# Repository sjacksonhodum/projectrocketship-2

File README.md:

# projectrocketship
## But this time version 2 :0

Check R1 on sensor board. 732kohm??? add whatever the right value is to the current lcsc cart

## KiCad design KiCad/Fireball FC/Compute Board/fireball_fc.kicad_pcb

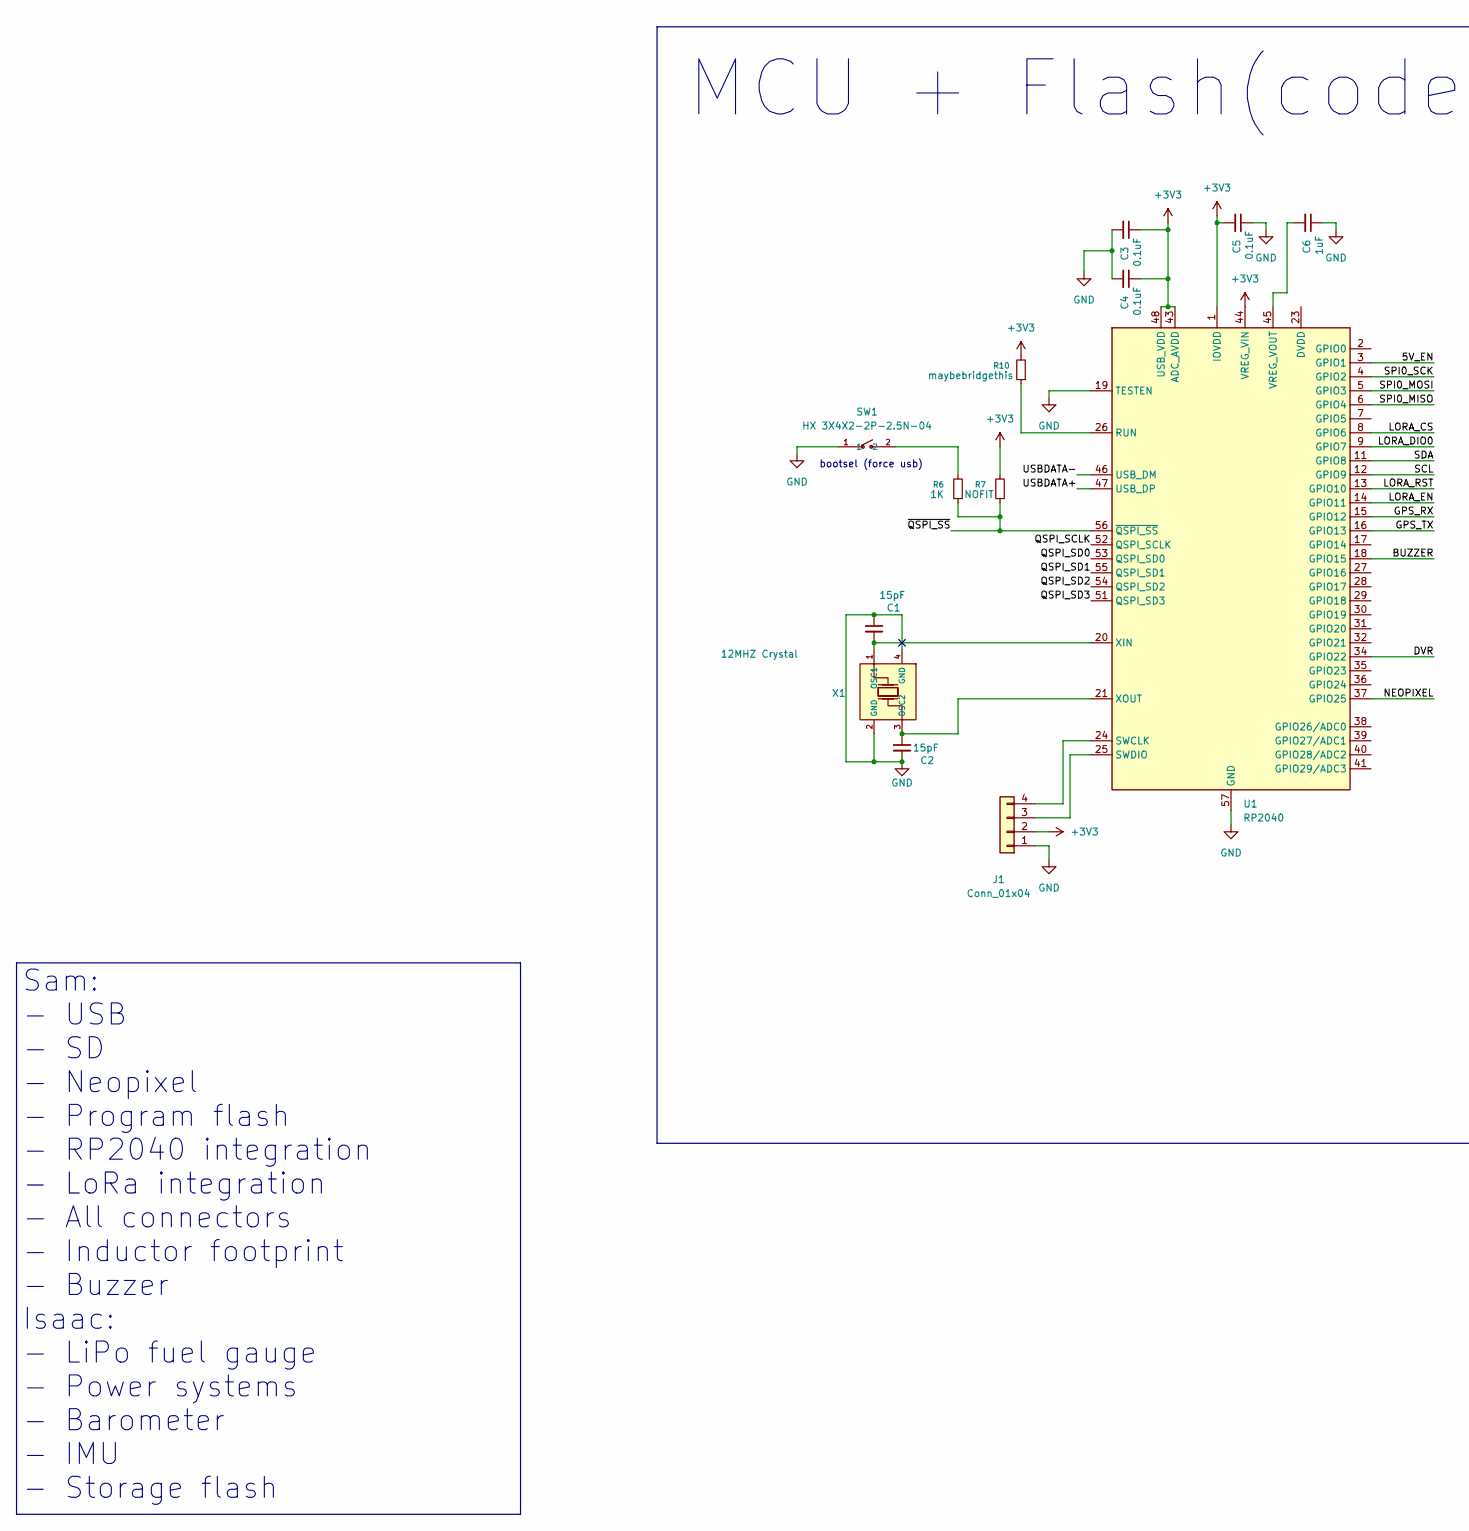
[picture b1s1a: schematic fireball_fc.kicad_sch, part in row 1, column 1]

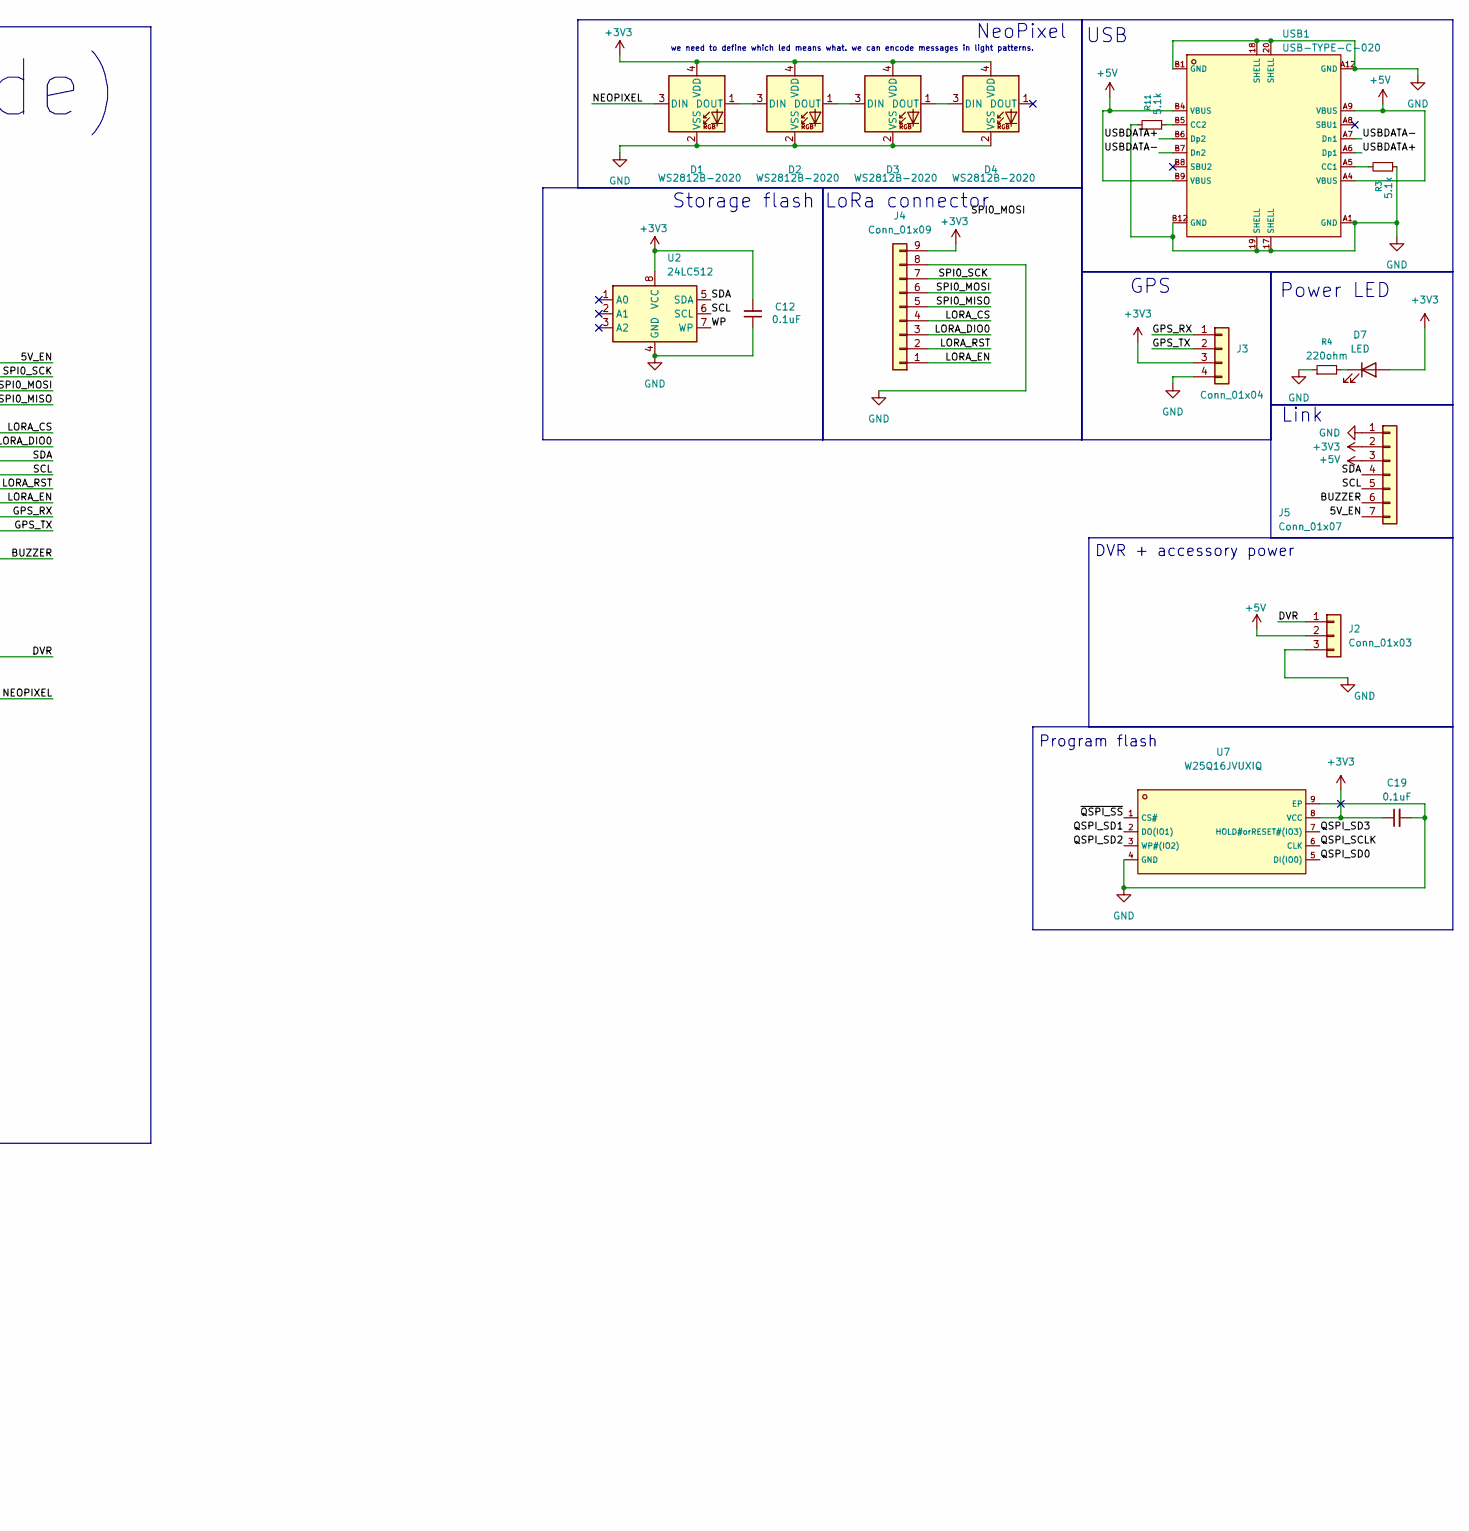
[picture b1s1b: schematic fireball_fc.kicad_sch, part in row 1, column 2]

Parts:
C1, C2: 15pF; C_0402_1005Metric
C3, C4, C5, C12, C19: 0.1uF; C_0402_1005Metric
C6: 1uF; C_0603_1608Metric
D1, D2, D3, D4: WS2812B-2020; LED_WS2812B-2020_PLCC4_2.0x2.0mm
D7: LED; LED_0805_2012Metric
J1, J3: Conn_01x04; PinHeader_1x04_P2.00mm_Vertical
J2: Conn_01x03; PinHeader_1x03_P2.00mm_Vertical
J4: Conn_01x09; PinHeader_1x09_P2.00mm_Vertical
J5: Conn_01x07; PinSocket_1x07_P2.00mm_Vertical
R3, R11: 5.1k; R_0402_1005Metric
R4: 220ohm; R_0402_1005Metric
R6: 1K; R_0402_1005Metric
R7: NOFIT; R_0402_1005Metric
R10: maybebridgethis; R_0402_1005Metric
SW1: HX 3X4X2-2P-2.5N-04; C54407262_SW-SMD_L4_0-W3_0-LS5_0; LCSC C54407262
U1: RP2040; QFN-56-1EP_7x7mm_P0.4mm_EP3.2x3.2mm
U2: 24LC512; SOIC-8-1EP_3.9x4.9mm_P1.27mm_EP2.29x3mm
U7: W25Q16JVUXIQ; C2843335_USON-8_L3_0-W2_0-P0_50-BL-EP; LCSC C2843335
USB1: USB-TYPE-C-020; C2927040_USB-SMD_USB-TYPE-C-020; LCSC C2927040
X1: 12MHZ Crystal; C157341_OSC-SMD_4P-L5_0-W3_2-BL; LCSC C5575013

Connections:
+3V3: C3.1, C4.1, C5.2, C12.2, C19.1, D1.4 (VDD), D2.4 (VDD), D3.4 (VDD), D4.4 (VDD), D7.2 (A), J1.2, J3.3, J4.9, J5.2, R7.2, R10.2, U1.1 (IOVDD), U1.10 (IOVDD), U1.22 (IOVDD), U1.33 (IOVDD), U1.42 (IOVDD), U1.43 (ADC_AVDD), U1.44 (VREG_VIN), U1.48 (USB_VDD), U1.49 (IOVDD), U2.8 (VCC), U7.8 (VCC); also elsewhere on the board
+5V: J2.2, J5.3, USB1.A4 (VBUS), USB1.A9 (VBUS), USB1.B4 (VBUS), USB1.B9 (VBUS)
/5V_EN: J5.7, U1.3 (GPIO1)
/BUZZER: J5.6, U1.18 (GPIO15)
/DVR: J2.1, U1.34 (GPIO22)
/GPS_RX: J3.1, U1.15 (GPIO12)
/GPS_TX: J3.2, U1.16 (GPIO13)
/LORA_CS: J4.4, U1.8 (GPIO6)
/LORA_DIO0: J4.3, U1.9 (GPIO7)
/LORA_EN: J4.1, U1.14 (GPIO11)
/LORA_RST: J4.2, U1.13 (GPIO10)
/NEOPIXEL: D1.3 (DIN), U1.37 (GPIO25)
/QSPI_SCLK: U1.52 (QSPI_SCLK), U7.6 (CLK)
/QSPI_SD0: U1.53 (QSPI_SD0), U7.5 (DI(IO0))
/QSPI_SD1: U1.55 (QSPI_SD1), U7.2 (DO(IO1))
/QSPI_SD2: U1.54 (QSPI_SD2), U7.3 (WP#(IO2))
/QSPI_SD3: U1.51 (QSPI_SD3), U7.7 (HOLD#orRESET#(IO3))
/SCL: J5.5, U1.12 (GPIO9), U2.6 (SCL)
/SDA: J5.4, U1.11 (GPIO8), U2.5 (SDA)
/SPI0_MISO: J4.5, U1.6 (GPIO4)
/SPI0_MOSI: J4.6, U1.5 (GPIO3)
/SPI0_SCK: J4.7, U1.4 (GPIO2)
/USBDATA+: U1.47 (USB_DP), USB1.A6 (Dp1), USB1.B6 (Dp2)
/USBDATA-: U1.46 (USB_DM), USB1.A7 (Dn1), USB1.B7 (Dn2)
/WP: U2.7 (WP)
/~QSPI_SS: R6.1, R7.1, U1.56 (~QSPI_SS), U7.1 (CS#)
GND: C1.1, C2.2, C3.2, C4.2, C5.1, C6.1, C12.1, C19.2, D1.2 (VSS), D2.2 (VSS), D3.2 (VSS), D4.2 (VSS), J1.1, J2.3, J3.4, J4.8, J5.1, R3.1, R4.1, R11.2, SW1.1, U1.19 (TESTEN), U1.57 (GND), U2.4 (GND), U7.4 (GND), U7.9 (EP), USB1.17 (SHELL), USB1.18 (SHELL), USB1.19 (SHELL), USB1.20 (SHELL), USB1.A1 (GND), USB1.A12 (GND), USB1.B1 (GND), USB1.B12 (GND), X1.2 (GND), X1.4 (GND); also elsewhere on the board
unnamed: D1.1 (DOUT), D2.3 (DIN)
unnamed: D2.1 (DOUT), D3.3 (DIN)
unnamed: D3.1 (DOUT), D4.3 (DIN)
unnamed: D7.1 (K), R4.2
unnamed: J1.3, U1.25 (SWDIO)
unnamed: J1.4, U1.24 (SWCLK)
unnamed: R6.2, SW1.2
unnamed: U1.23 (DVDD), U1.50 (DVDD)
unnamed: R10.1, U1.26 (RUN)
unnamed: C6.2, U1.45 (VREG_VOUT)
unnamed: C1.2, U1.20 (XIN), X1.1 (OSC1)
unnamed: C2.1, U1.21 (XOUT), X1.3 (OSC2)
unnamed: R3.2, USB1.A5 (CC1)
unnamed: R11.1, USB1.B5 (CC2)

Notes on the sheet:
Storage flash
MCU + Flash(code)
DVR + accessory power
bootsel (force usb)
USB
LoRa connector
we need to define which led means what. we can encode messages in light patterns.
Power LED
NeoPixel
Link
Program flash
GPS
Sam: - USB - SD - Neopixel - Program flash - RP2040 integration - LoRa integration - All connectors - Inductor footprint - Buzzer Isaac: - LiPo fuel gauge - Power systems - Barometer - IMU - Storage flash

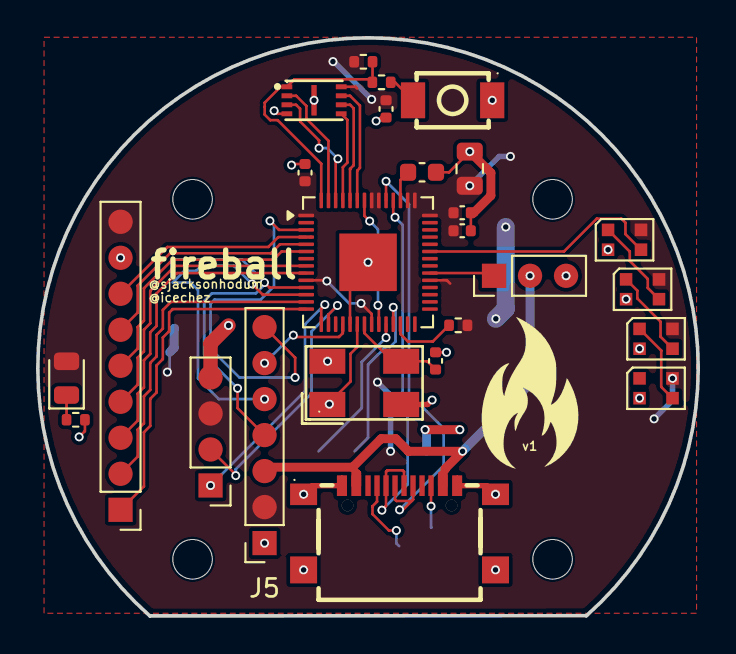
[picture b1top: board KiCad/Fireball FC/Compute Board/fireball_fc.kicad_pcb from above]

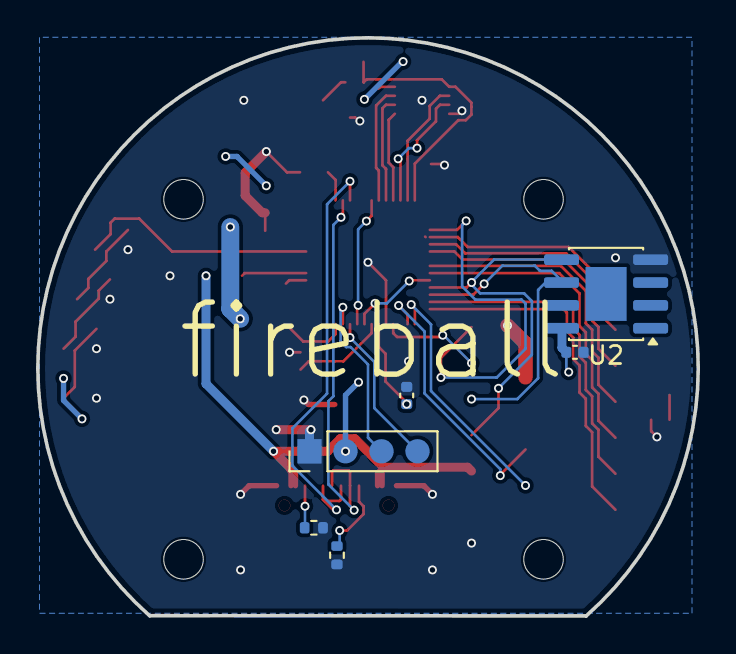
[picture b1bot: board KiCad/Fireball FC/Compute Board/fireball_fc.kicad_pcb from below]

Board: 2 copper layers, 36.7 x 32.1 mm, 35 parts (6 on the bottom side), 40 nets.

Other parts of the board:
C22: 10uF; C_0805_2012Metric
M1, M2, M3, M4: MountingHole_2.2mm_M2

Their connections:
+3V3: C22.2; also elsewhere on the board
GND: C22.1; also elsewhere on the board

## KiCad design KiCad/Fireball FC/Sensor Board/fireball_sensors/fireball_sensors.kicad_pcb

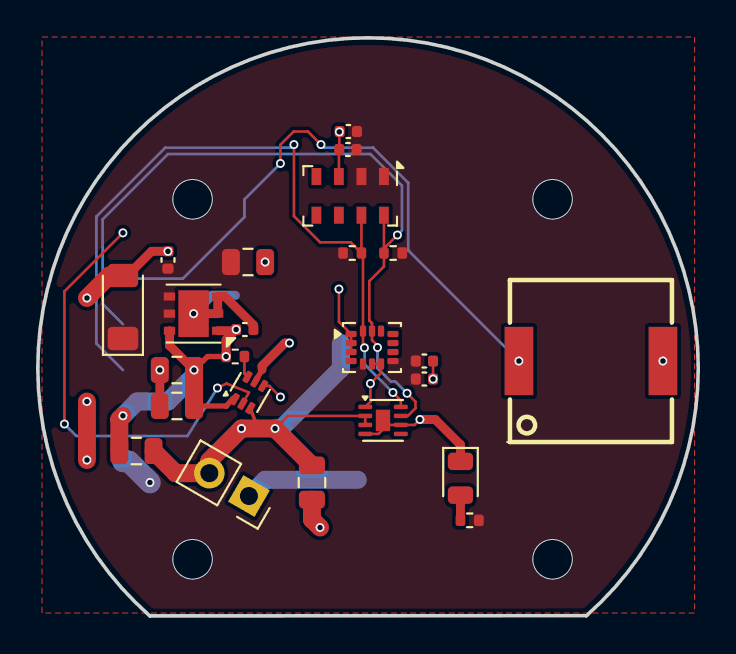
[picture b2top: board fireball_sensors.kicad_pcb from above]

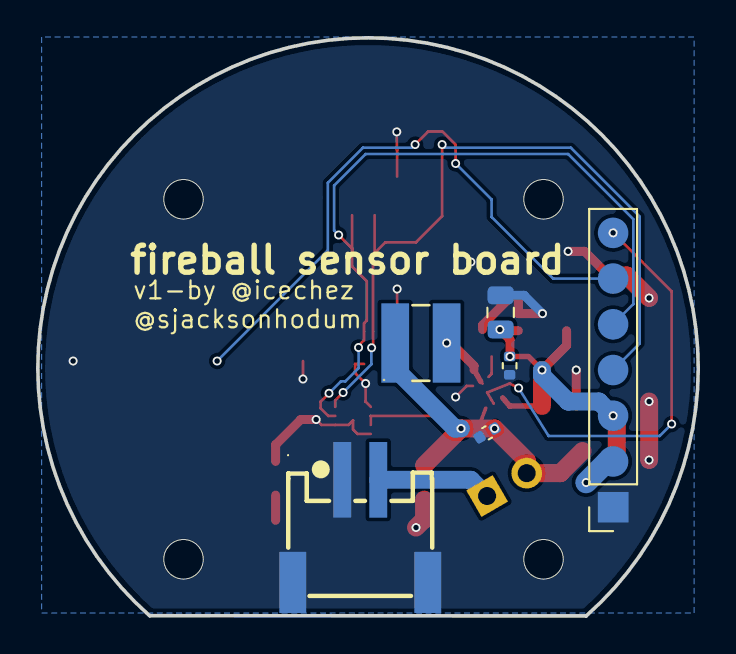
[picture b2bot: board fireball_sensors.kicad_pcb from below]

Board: 2 copper layers, 36.7 x 32.1 mm, 34 parts (6 on the bottom side), 12 nets.

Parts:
BUZ1: CPT-9019S-SMT-TR; C95163_BUZ-SMD_L9_0-W9_0-P8_00-LS9_3
C7, C13, C15, C16, C17, C18, C20: 0.1uF; C_0402_1005Metric
C8: 10uF; C_0805_2012Metric
C9, C10: 22uF; C_0805_2012Metric
C11: 4.7uF; C_0805_2012Metric
C14: 1uF; C_0805_2012Metric
CN1: HDGC2001WR-S-2P; C2936224_CONN-SMD_2P-P2_00_HDGC_HDGC2001WR-S-2P
D1: LED_Small; LED_0805_2012Metric
D5: BZV55B5V1; D_MiniMELF
D6: D; C_0805_2012Metric
J1: Conn_01x07; PinSocket_1x07_P2.54mm_Vertical
L2: FTC404030S1R0MGCA; C39676079_IND-SMD_L4_1-W4_1_SPM40XX
M1, M2, M3, M4: MountingHole_2.2mm_M2
R1: 732k; R_0402_1005Metric
R2: 100k; R_0402_1005Metric
R3: R_Small; R_0402_1005Metric
R8, R9: 4.7k; R_0402_1005Metric
SW2: MAIN POWER; PinSocket_1x02_P2.54mm_Vertical
U2: MAX17048G; TDFN-8-1EP_2x2mm_P0.5mm_EP0.8x1.2mm
U3: TPS61023; SOT-563
U5: NCP708; DFN-6-1EP_3x3mm_P0.95mm_EP1.7x2.6mm
U8: LSM6DSO; LGA-14_3x2.5mm_P0.5mm_LayoutBorder3x4y
U9: MS5607-02BA; LGA-8_3x5mm_P1.25mm

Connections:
+3V3: C11.1, C13.2, C16.2, C17.2, C18.1, C20.1, D5.1 (K), J1.2, R3.1, R8.2, R9.2, U5.4 (OUT), U5.5 (OUT_S), U8.5 (VDDIO), U8.8 (VDD), U9.1 (VDD), U9.2 (PS)
+5V: C9.2, C10.2, C14.1, C15.2, D6.1 (K), J1.3, R1.2, R2.2, U3.1 (FB), U5.1 (EN), U5.6 (IN)
+BATT: C7.2, C8.2, D6.2 (A), L2.1, SW2.2 (B), U2.2 (CELL), U2.3 (VDD), U3.3 (VIN)
/5V_EN: J1.7, U3.2 (EN)
/BUZZER: BUZ1.1 (+), J1.6
/SCL: J1.5, R9.1, U2.7 (SCL), U8.13 (SCL), U9.8 (SCLK)
/SDA: J1.4, R8.1, U2.8 (SDA), U8.14 (SDA), U9.7 (SDI/SDA)
GND: BUZ1.2 (-), C7.1, C8.1, C9.1, C10.1, C11.2, C13.1, C14.2, C15.1, C16.1, C17.1, C18.2, C20.2, CN1.1, CN1.3, CN1.4, D1.1 (K), D5.2 (A), J1.1, R2.1, U2.1 (CTG), U2.4 (GND), U2.6 (Q), U2.9 (PAD), U3.4 (GND), U5.2 (GND), U5.3 (N/C), U5.7 (PAD), U8.1 (SDO/SA0), U8.2 (SDX), U8.3 (SCX), U8.6 (GND), U8.7 (GND), U9.3 (GND)
unnamed: D1.2 (A), R3.2
unnamed: CN1.2, SW2.1 (A)
unnamed: L2.2, U3.5 (SW)
unnamed: R1.1, U3.6 (VOUT)

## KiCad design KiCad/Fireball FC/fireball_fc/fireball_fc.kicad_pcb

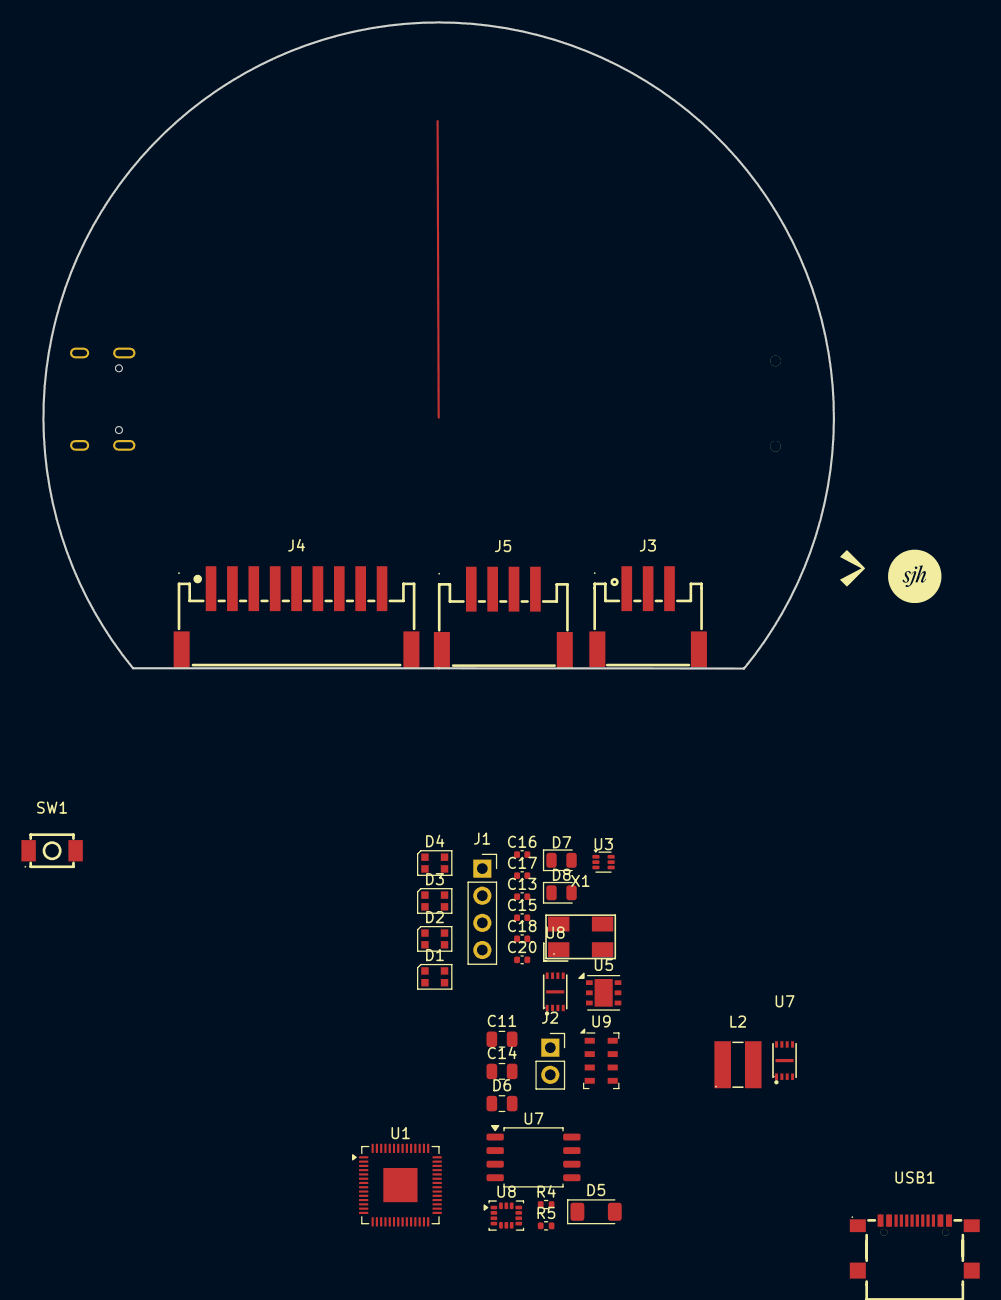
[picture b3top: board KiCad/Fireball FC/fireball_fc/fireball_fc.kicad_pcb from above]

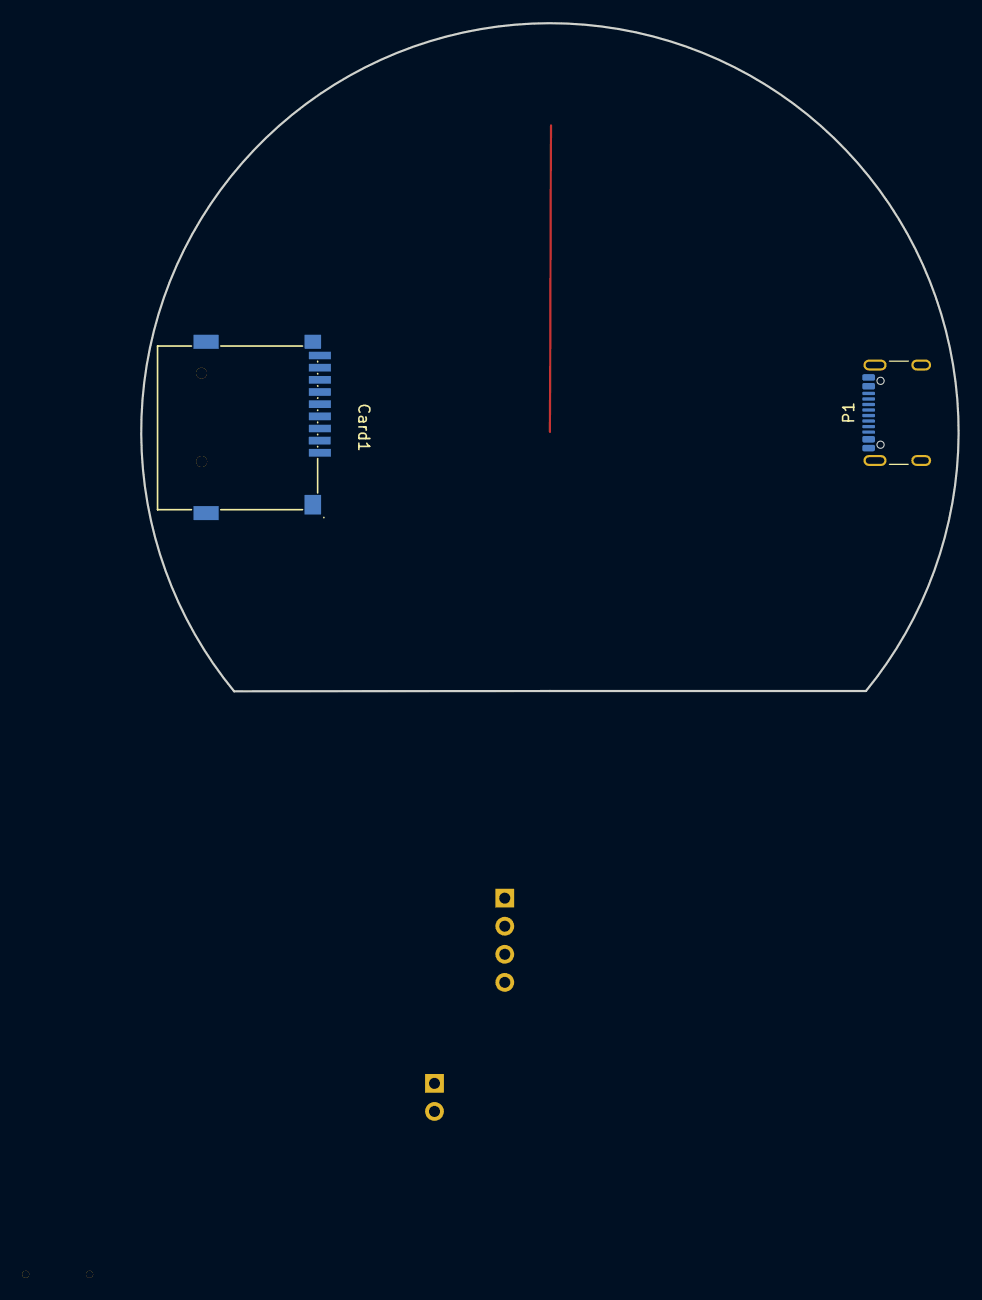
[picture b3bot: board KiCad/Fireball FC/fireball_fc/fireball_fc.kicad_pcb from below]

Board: 2 copper layers, 74.0 x 60.5 mm, 37 parts (2 on the bottom side), 29 nets, no tracks yet.

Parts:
C11: 4.7uF; C_0805_2012Metric
C13, C15, C16, C17, C18, C20: 0.1uF; C_0402_1005Metric
C14: 1uF; C_0805_2012Metric
Card1: HYC77-TF09-200; C341092_TF-SMD_HYC77-TF09-200
D1, D2, D3, D4: WS2812B-2020; LED_WS2812B-2020_PLCC4_2.0x2.0mm
D5: BZV55B5V1; D_MiniMELF
D6: D; C_0805_2012Metric
D7, D8: LED; LED_0805_2012Metric
J1: Conn_01x04; PinSocket_1x04_P2.54mm_Vertical
J2: Conn_01x02; PinSocket_1x02_P2.54mm_Vertical
J3: HDGC2001WR-S-3P; C2936225_CONN-SMD_3P-P2_00_HDGC_HDGC2001WR-S-3P
J4: HDGC2001WR-S-9P; C5175304_CONN-SMD_9P-P2_00_HDGC_HDGC2001WR-S-9P
J5: HDGC2001WR-S-4P; C2936226_CONN-SMD_4P-P2_00_HDGC_HDGC2001WR-S-4P
L2: FTC404030S1R0MGCA; C39676079_IND-SMD_L4_1-W4_1_SPM40XX
P1: USB_C_Plug_USB2.0; USB_C_Receptacle_GCT_USB4105-xx-A_16P_TopMnt_Horizontal
R4, R5: 220ohm; R_0402_1005Metric
SW1: HX 3X4X2-2P-2.5N-04; C54407262_SW-SMD_L4_0-W3_0-LS5_0
U1: RP2040; QFN-56-1EP_7x7mm_P0.4mm_EP3.2x3.2mm
U3: TPS61023; SOT-563
U5: NCP708; DFN-6-1EP_3x3mm_P0.95mm_EP1.7x2.6mm
U7: W25Q128JVS; SOIC-8_5.3x5.3mm_P1.27mm
U7#2, U8#2: W25Q16JVUXIQ; C2843335_USON-8_L3_0-W2_0-P0_50-BL-EP
U8: LSM6DSO; LGA-14_3x2.5mm_P0.5mm_LayoutBorder3x4y
U9: MS5607-02BA; LGA-8_3x5mm_P1.25mm
USB1: USB-TYPE-C-020; C2927040_USB-SMD_USB-TYPE-C-020
X1: 12MHZ Crystal; C157341_OSC-SMD_4P-L5_0-W3_2-BL

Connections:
+3V3: C11.1, C13.2, C16.2, C17.2, C18.1, C20.1, D1.4 (VDD), D2.4 (VDD), D3.4 (VDD), D4.4 (VDD), D5.1 (K), D7.2 (A), J1.2, J4.9, U1.1 (IOVDD), U1.10 (IOVDD), U1.22 (IOVDD), U1.33 (IOVDD), U1.42 (IOVDD), U1.43 (ADC_AVDD), U1.44 (VREG_VIN), U1.48 (USB_VDD), U1.49 (IOVDD), U5.4 (OUT), U5.5 (OUT_S), U7.8 (VCC), U7#2.8 (VCC), U8.5 (VDDIO), U8.8 (VDD), U8#2.8 (VCC), U9.1 (VDD), U9.2 (PS)
+5V: C14.1, C15.2, D6.1 (K), J3.2, P1.A4 (VBUS), P1.A9 (VBUS), P1.B4 (VBUS), P1.B9 (VBUS), U3.1 (FB), U5.1 (EN), U5.6 (IN), USB1.A4 (VBUS), USB1.A9 (VBUS), USB1.B4 (VBUS), USB1.B9 (VBUS)
+BATT: D6.2 (A), L2.1, U3.3 (VIN)
/GPS_RX: J5.1, U1.15 (GPIO12)
/GPS_TX: J5.2, U1.16 (GPIO13)
/NEOPIXEL: D1.3 (DIN), U1.17 (GPIO14)
/QSPI_SCLK: U1.52 (QSPI_SCLK), U7#2.6 (CLK)
/QSPI_SD0: U1.53 (QSPI_SD0), U7#2.5 (DI(IO0))
/QSPI_SD1: U1.55 (QSPI_SD1), U7#2.2 (DO(IO1))
/QSPI_SD2: U1.54 (QSPI_SD2), U7#2.3 (WP#(IO2))
/QSPI_SD3: U1.51 (QSPI_SD3), U7#2.7 (HOLD#orRESET#(IO3))
/SCL: U1.12 (GPIO9), U8.13 (SCL), U9.8 (SCLK)
/SDA: U1.11 (GPIO8), U8.14 (SDA), U9.7 (SDI/SDA)
/SDLED: D8.2 (A), U1.27 (GPIO16)
/USBDATA+: P1.A6 (D+), U1.47 (USB_DP), USB1.A6 (Dp1), USB1.B6 (Dp2)
/USBDATA-: P1.A7 (D-), U1.46 (USB_DM), USB1.A7 (Dn1), USB1.B7 (Dn2)
/~QSPI_SS: U1.56 (~QSPI_SS), U7#2.1 (CS#)
GND: C11.2, C13.1, C14.2, C15.1, C16.1, C17.1, C18.2, C20.2, Card1.10, Card1.11, Card1.12, Card1.13, D1.2 (VSS), D2.2 (VSS), D3.2 (VSS), D4.2 (VSS), D5.2 (A), J1.1, J2.1, J3.3, J3.4, J3.5, J4.8, J4.10, J4.11, J5.4, J5.5, J5.6, P1.A1 (GND), P1.A12 (GND), P1.B1 (GND), P1.B12 (GND), P1.SH (SHIELD), R4.1, R5.1, SW1.1, U1.19 (TESTEN), U1.57 (GND), U3.4 (GND), U5.2 (GND), U5.3 (N/C), U5.7 (PAD), U7.4 (GND), U7#2.4 (GND), U7#2.9 (EP), U8.1 (SDO/SA0), U8.2 (SDX), U8.3 (SCX), U8.6 (GND), U8.7 (GND), U8#2.4 (GND), U8#2.9 (EP), U9.3 (GND), USB1.17 (SHELL), USB1.18 (SHELL), USB1.19 (SHELL), USB1.20 (SHELL), USB1.A1 (GND), USB1.A12 (GND), USB1.B1 (GND), USB1.B12 (GND), X1.2 (GND), X1.4 (GND)
unnamed: D1.1 (DOUT), D2.3 (DIN)
unnamed: D2.1 (DOUT), D3.3 (DIN)
unnamed: D3.1 (DOUT), D4.3 (DIN)
unnamed: D7.1 (K), R4.2
unnamed: D8.1 (K), R5.2
unnamed: J1.3, U1.25 (SWDIO)
unnamed: J1.4, U1.24 (SWCLK)
unnamed: U1.23 (DVDD), U1.50 (DVDD)
unnamed: U1.20 (XIN), X1.1 (OSC1)
unnamed: U1.21 (XOUT), X1.3 (OSC2)
unnamed: L2.2, U3.5 (SW)

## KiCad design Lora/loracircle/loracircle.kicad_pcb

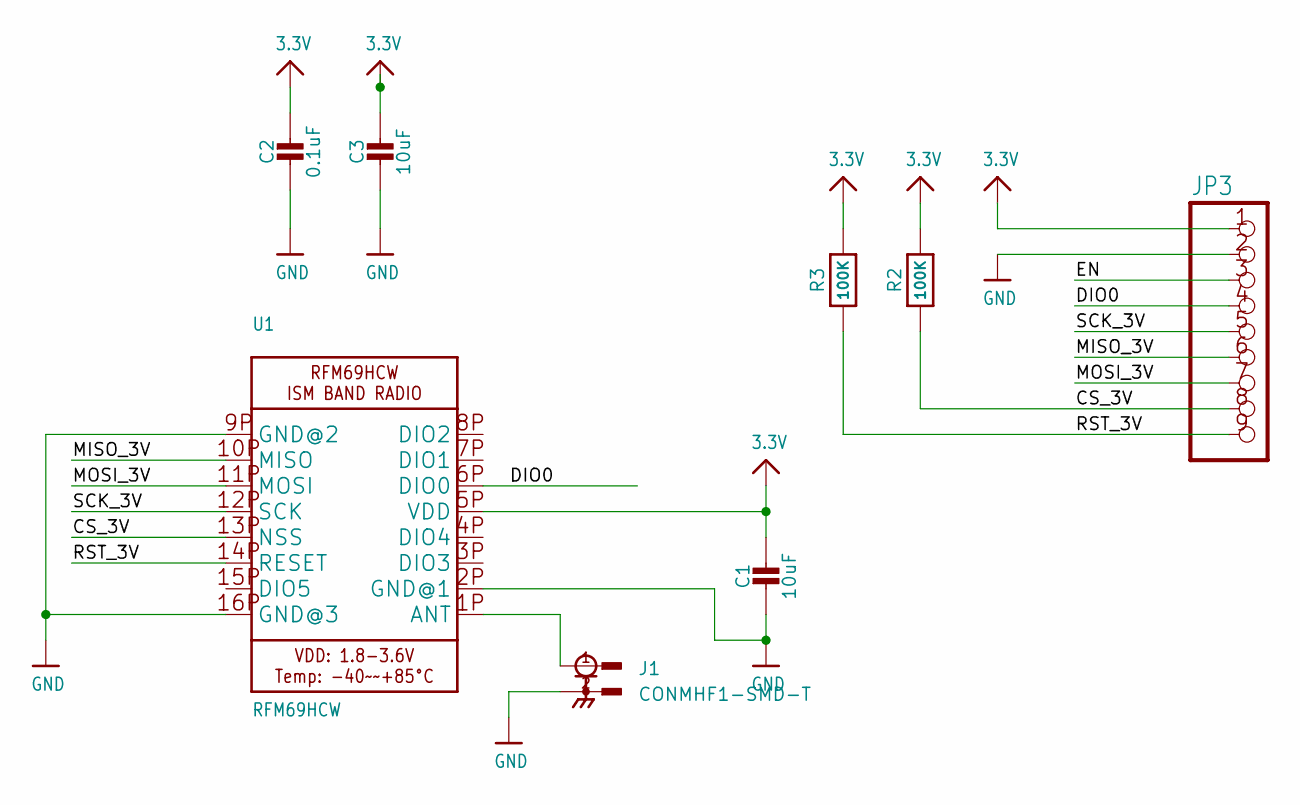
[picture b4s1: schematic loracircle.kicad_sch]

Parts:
C1, C3: 10uF; 0805-NO
C2: 0.1uF; 0805-NO
J1: CONMHF1-SMD-T; TE_CONMHF1-SMD-T; PARTREV 09/22
JP3: HEADER-1X970MIL; CONN_B9B-PH-SM4-TB_JST
R2, R3: 100K; 0805-NO
U1: RFM69HCW; RFMHCW_SMT

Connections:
3.3V: C1.1, C2.1, C3.1, JP3.1, R2.2, R3.2, U1.5P (VDD)
/CS_3V: JP3.8, R2.1, U1.13P (NSS)
/DIO0: JP3.4, U1.6P (DIO0)
/EN: JP3.3
/MISO_3V: JP3.6, U1.10P (MISO)
/MOSI_3V: JP3.7, U1.11P (MOSI)
/RST_3V: JP3.9, R3.1, U1.14P (RESET)
/SCK_3V: JP3.5, U1.12P (SCK)
GND: C1.2, C2.2, C3.2, J1.2, J1.3, J1.4, JP3.2, U1.2P (GND@1), U1.9P (GND@2), U1.16P (GND@3)
unnamed: J1.1, U1.1P (ANT)

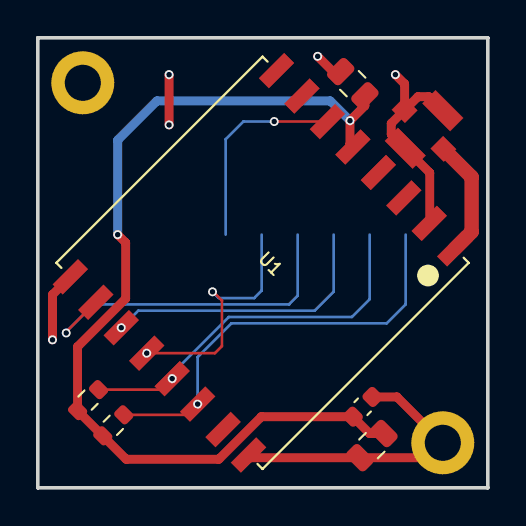
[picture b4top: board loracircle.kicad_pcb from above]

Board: 2 copper layers, 25.0 x 25.0 mm, 8 parts (1 on the bottom side), 9 nets.

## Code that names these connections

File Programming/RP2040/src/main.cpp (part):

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constexpr uint8_t RFM95_RST = 10;
constexpr uint8_t RFM95_INT = 7;

constexpr uint8_t LORA_EN_PIN = 11;

constexpr float RF95_FREQ_MHZ = 433.0;

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Adafruit_MAX17048 maxlipo;


constexpr uint8_t BUZZER_PIN = 15;


constexpr uint8_t NEOPIXEL_PIN = 25;
constexpr uint8_t NEOPIXEL_COUNT = 4;
constexpr uint8_t NEOPIXEL_BRIGHTNESS = 110;

Adafruit_NeoPixel pixels(NEOPIXEL_COUNT, NEOPIXEL_PIN, NEO_GRB + NEO_KHZ800);


struct TelemetryState {
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  buzzerPhase = phase;
  buzzerPhaseStartMs = now;
  if (phase == BuzzerPhase::TONE_ON) {
    analogWrite(BUZZER_PIN, buzzerMuted ? 0 : BUZZER_VOLUME);
  } else {
    analogWrite(BUZZER_PIN, 0);
  }
}

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void setBuzzerMuted(bool muted) {
  buzzerMuted = muted;
  if (muted && buzzerPhase == BuzzerPhase::TONE_ON) {
    analogWrite(BUZZER_PIN, 0);
  }
}

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        buzzerPattern = nullptr;
        buzzerPhase = BuzzerPhase::IDLE;
        buzzerEventActive = false;
        analogWrite(BUZZER_PIN, 0);
        return;
      }
    }
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  Serial.println("================================");

  Serial.println("[BOOT] buzzer/neopixel init...");
  pinMode(BUZZER_PIN, OUTPUT);
  analogWriteFreq(BUZZER_FREQ_HZ);
  pixels.begin();
  pixels.setBrightness(NEOPIXEL_BRIGHTNESS);
  pixels.show();
  Serial.println("[BOOT] buzzer/neopixel init OK");

  Serial.println("[BOOT] GPIO1 high...");
  pinMode(GPIO1_ALWAYS_HIGH_PIN, OUTPUT);
  digitalWrite(GPIO1_ALWAYS_HIGH_PIN, HIGH);
  Serial.println("[BOOT] GPIO1 high OK");

  constexpr bool DIAG_5V_START_DISABLED = true;
  Serial.println(DIAG_5V_START_DISABLED ? "[BOOT] 5V rail starting OFF (diagnostic)..." : "[BOOT] 5V rail enable...");
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  Serial.println(DIAG_5V_START_DISABLED ? "[BOOT] 5V rail OFF OK - send 5VON to enable" : "[BOOT] 5V rail enable OK");

  Serial.println("[BOOT] LORA_EN high...");
  pinMode(LORA_EN_PIN, OUTPUT);
  digitalWrite(LORA_EN_PIN, HIGH);
  Serial.println("[BOOT] LORA_EN high OK");

  Serial.println("[BOOT] DVR button pad floating (idle)...");
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    if (ubxBytesReceived < 10) {
      Serial.println(
          "WARNING: No GPS data received at all. Check that the GPS "
          "module is plugged in, wired to GPIO12/GPIO13, and configured "
          "for 115200 baud.");
    } else if (ubxValidMessageCount == 0) {
      Serial.print("WARNING: Receiving bytes but zero valid UBX messages since boot config (");
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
